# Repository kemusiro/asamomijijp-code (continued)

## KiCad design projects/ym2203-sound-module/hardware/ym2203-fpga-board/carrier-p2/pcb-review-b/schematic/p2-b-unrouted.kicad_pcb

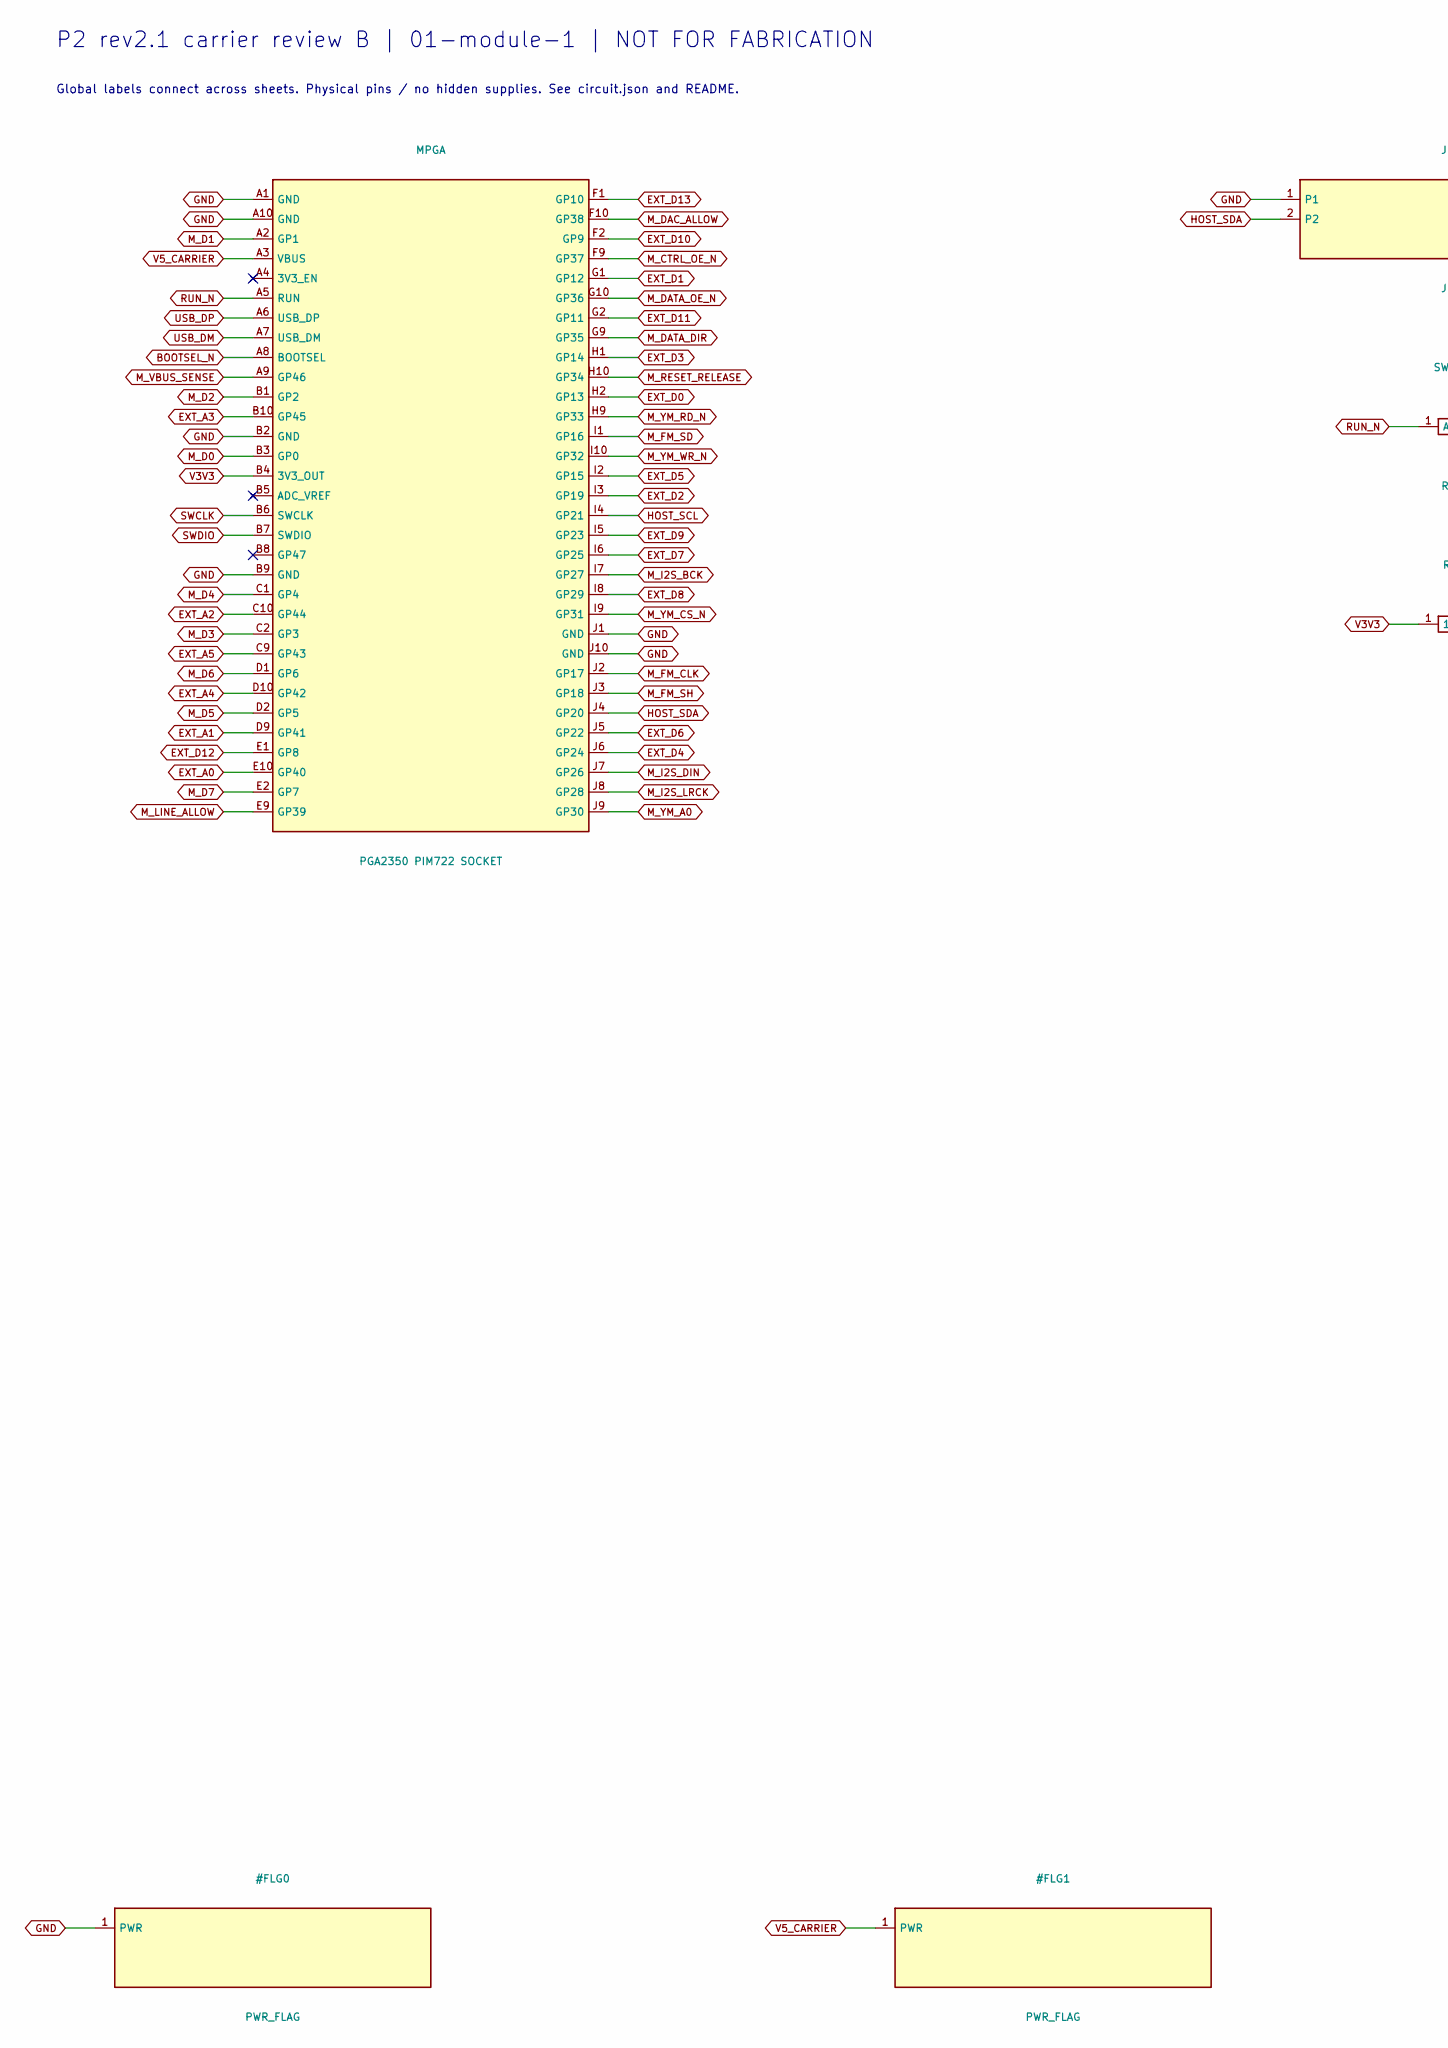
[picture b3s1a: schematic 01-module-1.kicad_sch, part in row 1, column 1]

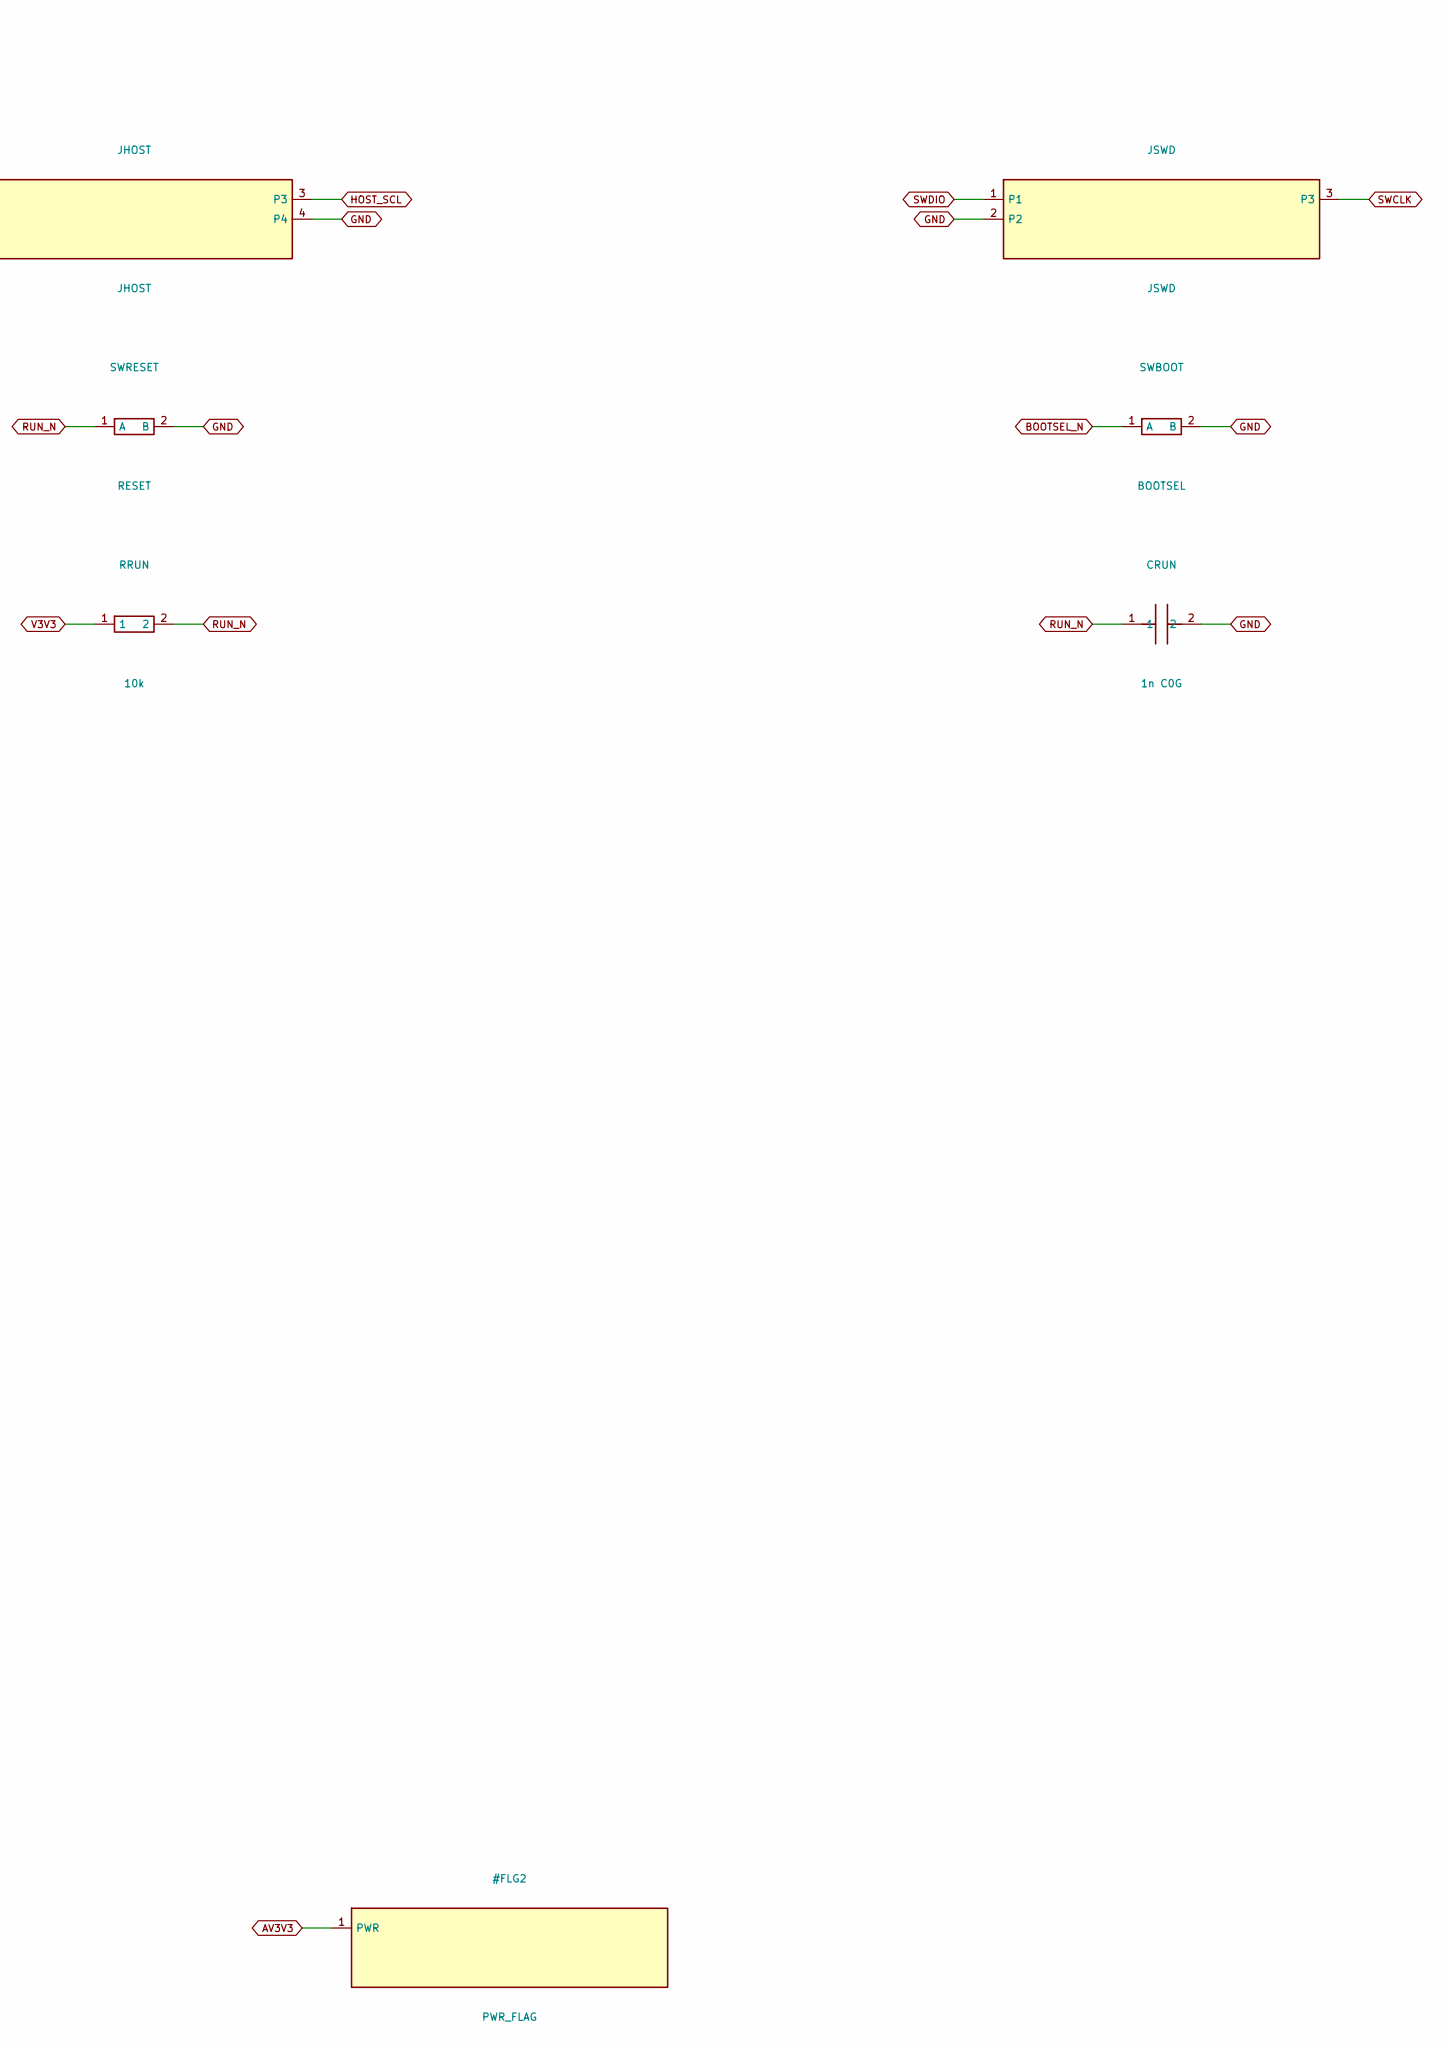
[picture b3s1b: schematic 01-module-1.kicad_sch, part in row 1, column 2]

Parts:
CRUN: 1n C0G; C_0805_2012Metric
JHOST: JHOST; PinHeader_1x04_P2.54mm_Vertical
JSWD: JSWD; PinHeader_1x03_P2.54mm_Vertical
MPGA: PGA2350 PIM722 SOCKET; PGA2350_Socket_64
RRUN: 10k; R_0805_2012Metric
SWBOOT: BOOTSEL; SW_PUSH_6mm_H4.3mm
SWRESET: RESET; SW_PUSH_6mm_H4.3mm

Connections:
BOOTSEL_N: MPGA.A8 (BOOTSEL), SWBOOT.1 (A)
EXT_A0: MPGA.E10 (GP40); also elsewhere on the board
EXT_A1: MPGA.D9 (GP41); also elsewhere on the board
EXT_A2: MPGA.C10 (GP44); also elsewhere on the board
EXT_A3: MPGA.B10 (GP45); also elsewhere on the board
EXT_A4: MPGA.D10 (GP42); also elsewhere on the board
EXT_A5: MPGA.C9 (GP43); also elsewhere on the board
EXT_D0: MPGA.H2 (GP13); also elsewhere on the board
EXT_D1: MPGA.G1 (GP12); also elsewhere on the board
EXT_D2: MPGA.I3 (GP19); also elsewhere on the board
EXT_D3: MPGA.H1 (GP14); also elsewhere on the board
EXT_D4: MPGA.J6 (GP24); also elsewhere on the board
EXT_D5: MPGA.I2 (GP15); also elsewhere on the board
EXT_D6: MPGA.J5 (GP22); also elsewhere on the board
EXT_D7: MPGA.I6 (GP25); also elsewhere on the board
EXT_D8: MPGA.I8 (GP29); also elsewhere on the board
EXT_D9: MPGA.I5 (GP23); also elsewhere on the board
EXT_D10: MPGA.F2 (GP9); also elsewhere on the board
EXT_D11: MPGA.G2 (GP11); also elsewhere on the board
EXT_D12: MPGA.E1 (GP8); also elsewhere on the board
EXT_D13: MPGA.F1 (GP10); also elsewhere on the board
GND: CRUN.2, JHOST.1, JHOST.4, JSWD.2, MPGA.A1 (GND), MPGA.A10 (GND), MPGA.B2 (GND), MPGA.B9 (GND), MPGA.J1 (GND), MPGA.J10 (GND), SWBOOT.2 (B), SWRESET.2 (B); also elsewhere on the board
HOST_SCL: JHOST.3, MPGA.I4 (GP21); also elsewhere on the board
HOST_SDA: JHOST.2, MPGA.J4 (GP20); also elsewhere on the board
M_CTRL_OE_N: MPGA.F9 (GP37); also elsewhere on the board
M_D0: MPGA.B3 (GP0); also elsewhere on the board
M_D1: MPGA.A2 (GP1); also elsewhere on the board
M_D2: MPGA.B1 (GP2); also elsewhere on the board
M_D3: MPGA.C2 (GP3); also elsewhere on the board
M_D4: MPGA.C1 (GP4); also elsewhere on the board
M_D5: MPGA.D2 (GP5); also elsewhere on the board
M_D6: MPGA.D1 (GP6); also elsewhere on the board
M_D7: MPGA.E2 (GP7); also elsewhere on the board
M_DAC_ALLOW: MPGA.F10 (GP38); also elsewhere on the board
M_DATA_DIR: MPGA.G9 (GP35); also elsewhere on the board
M_DATA_OE_N: MPGA.G10 (GP36); also elsewhere on the board
M_FM_CLK: MPGA.J2 (GP17); also elsewhere on the board
M_FM_SD: MPGA.I1 (GP16); also elsewhere on the board
M_FM_SH: MPGA.J3 (GP18); also elsewhere on the board
M_I2S_BCK: MPGA.I7 (GP27); also elsewhere on the board
M_I2S_DIN: MPGA.J7 (GP26); also elsewhere on the board
M_I2S_LRCK: MPGA.J8 (GP28); also elsewhere on the board
M_LINE_ALLOW: MPGA.E9 (GP39); also elsewhere on the board
M_RESET_RELEASE: MPGA.H10 (GP34); also elsewhere on the board
M_VBUS_SENSE: MPGA.A9 (GP46); also elsewhere on the board
M_YM_A0: MPGA.J9 (GP30); also elsewhere on the board
M_YM_CS_N: MPGA.I9 (GP31); also elsewhere on the board
M_YM_RD_N: MPGA.H9 (GP33); also elsewhere on the board
M_YM_WR_N: MPGA.I10 (GP32); also elsewhere on the board
RUN_N: CRUN.1, MPGA.A5 (RUN), RRUN.2, SWRESET.1 (A); also elsewhere on the board
SWCLK: JSWD.3, MPGA.B6 (SWCLK)
SWDIO: JSWD.1, MPGA.B7 (SWDIO)
USB_DM: MPGA.A7 (USB_DM); also elsewhere on the board
USB_DP: MPGA.A6 (USB_DP); also elsewhere on the board
V3V3: MPGA.B4 (3V3_OUT), RRUN.1; also elsewhere on the board
V5_CARRIER: MPGA.A3 (VBUS); also elsewhere on the board

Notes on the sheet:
P2 rev2.1 carrier review B | 01-module-1 | NOT FOR FABRICATION
Global labels connect across sheets. Physical pins / no hidden supplies. See circuit.json and README.

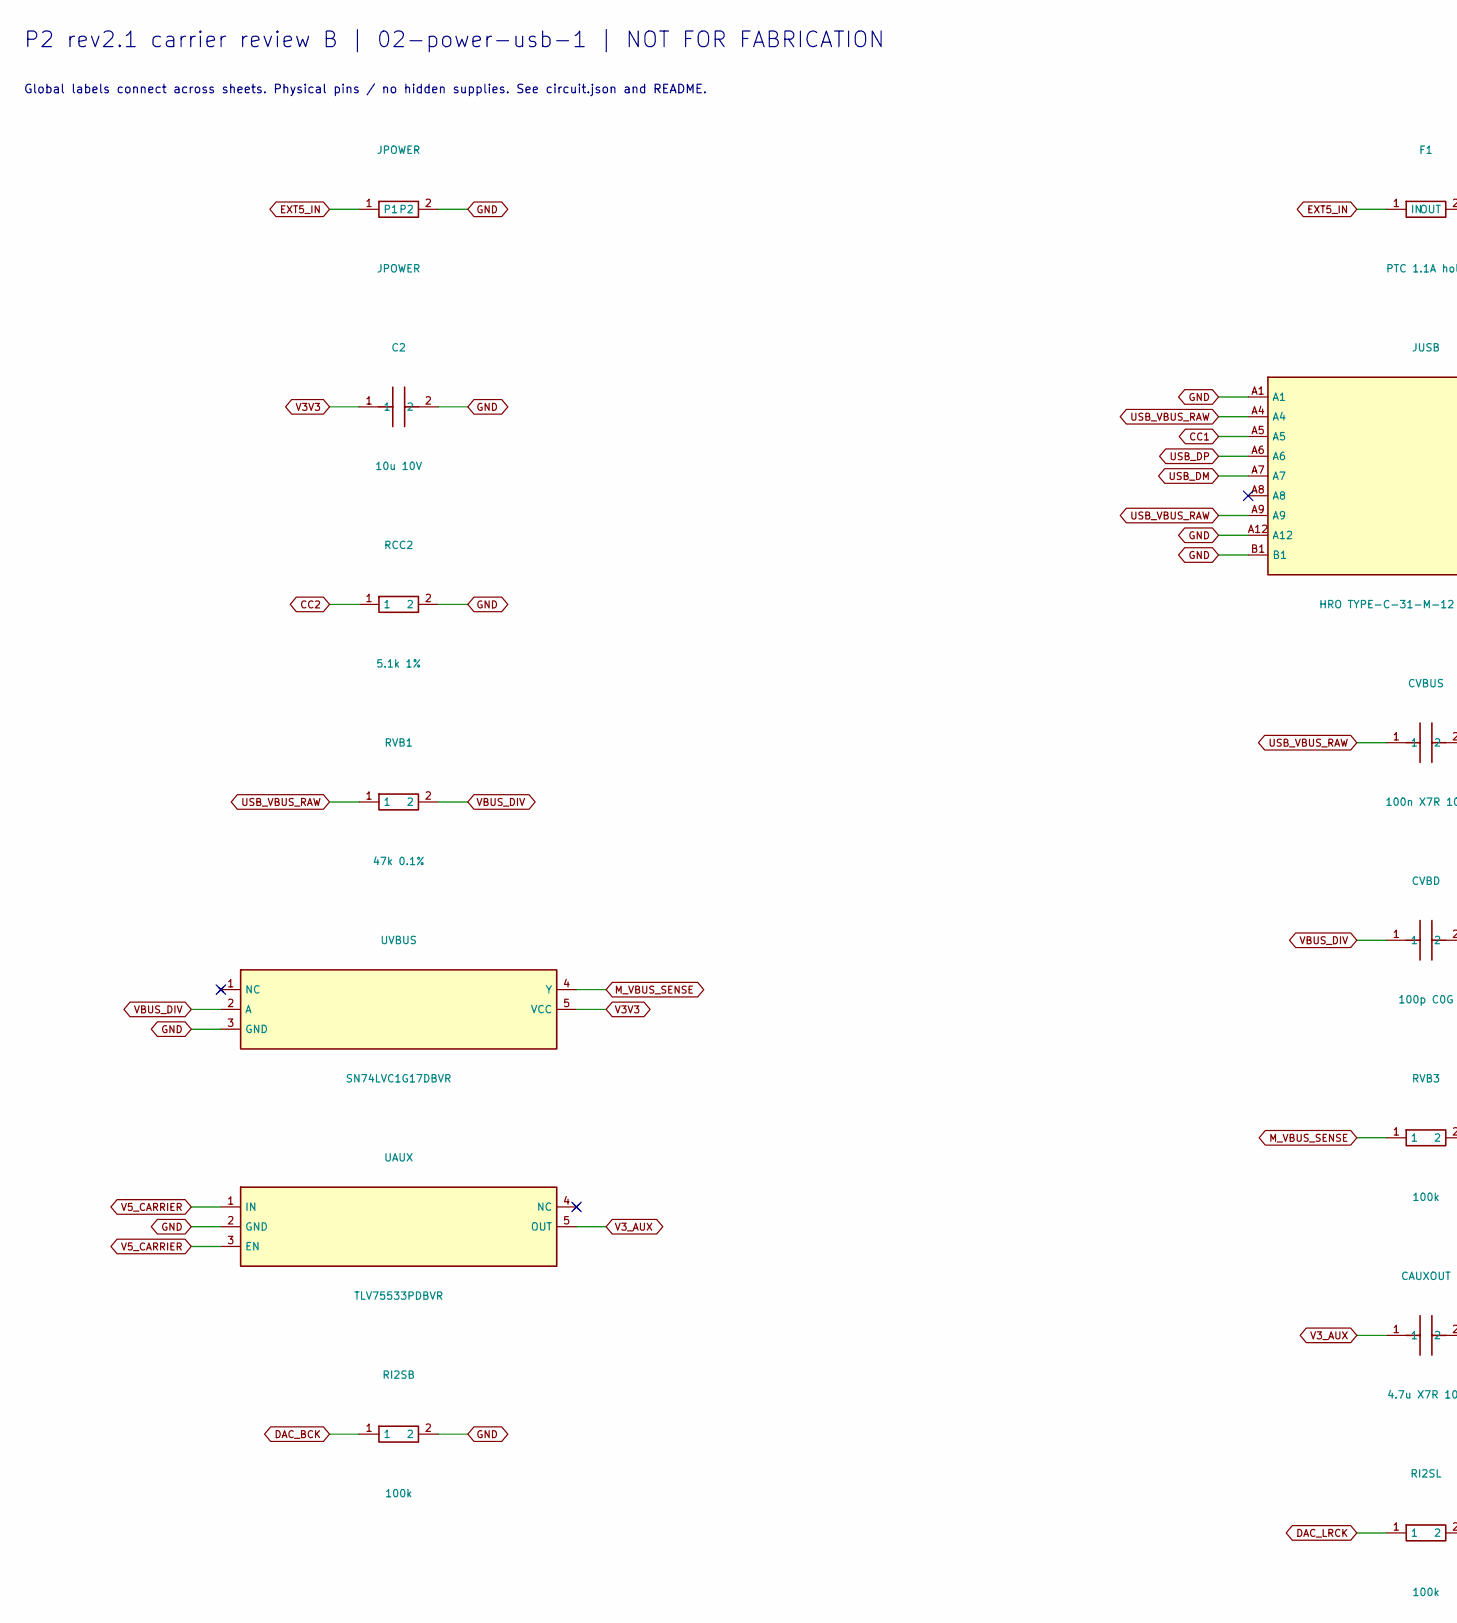
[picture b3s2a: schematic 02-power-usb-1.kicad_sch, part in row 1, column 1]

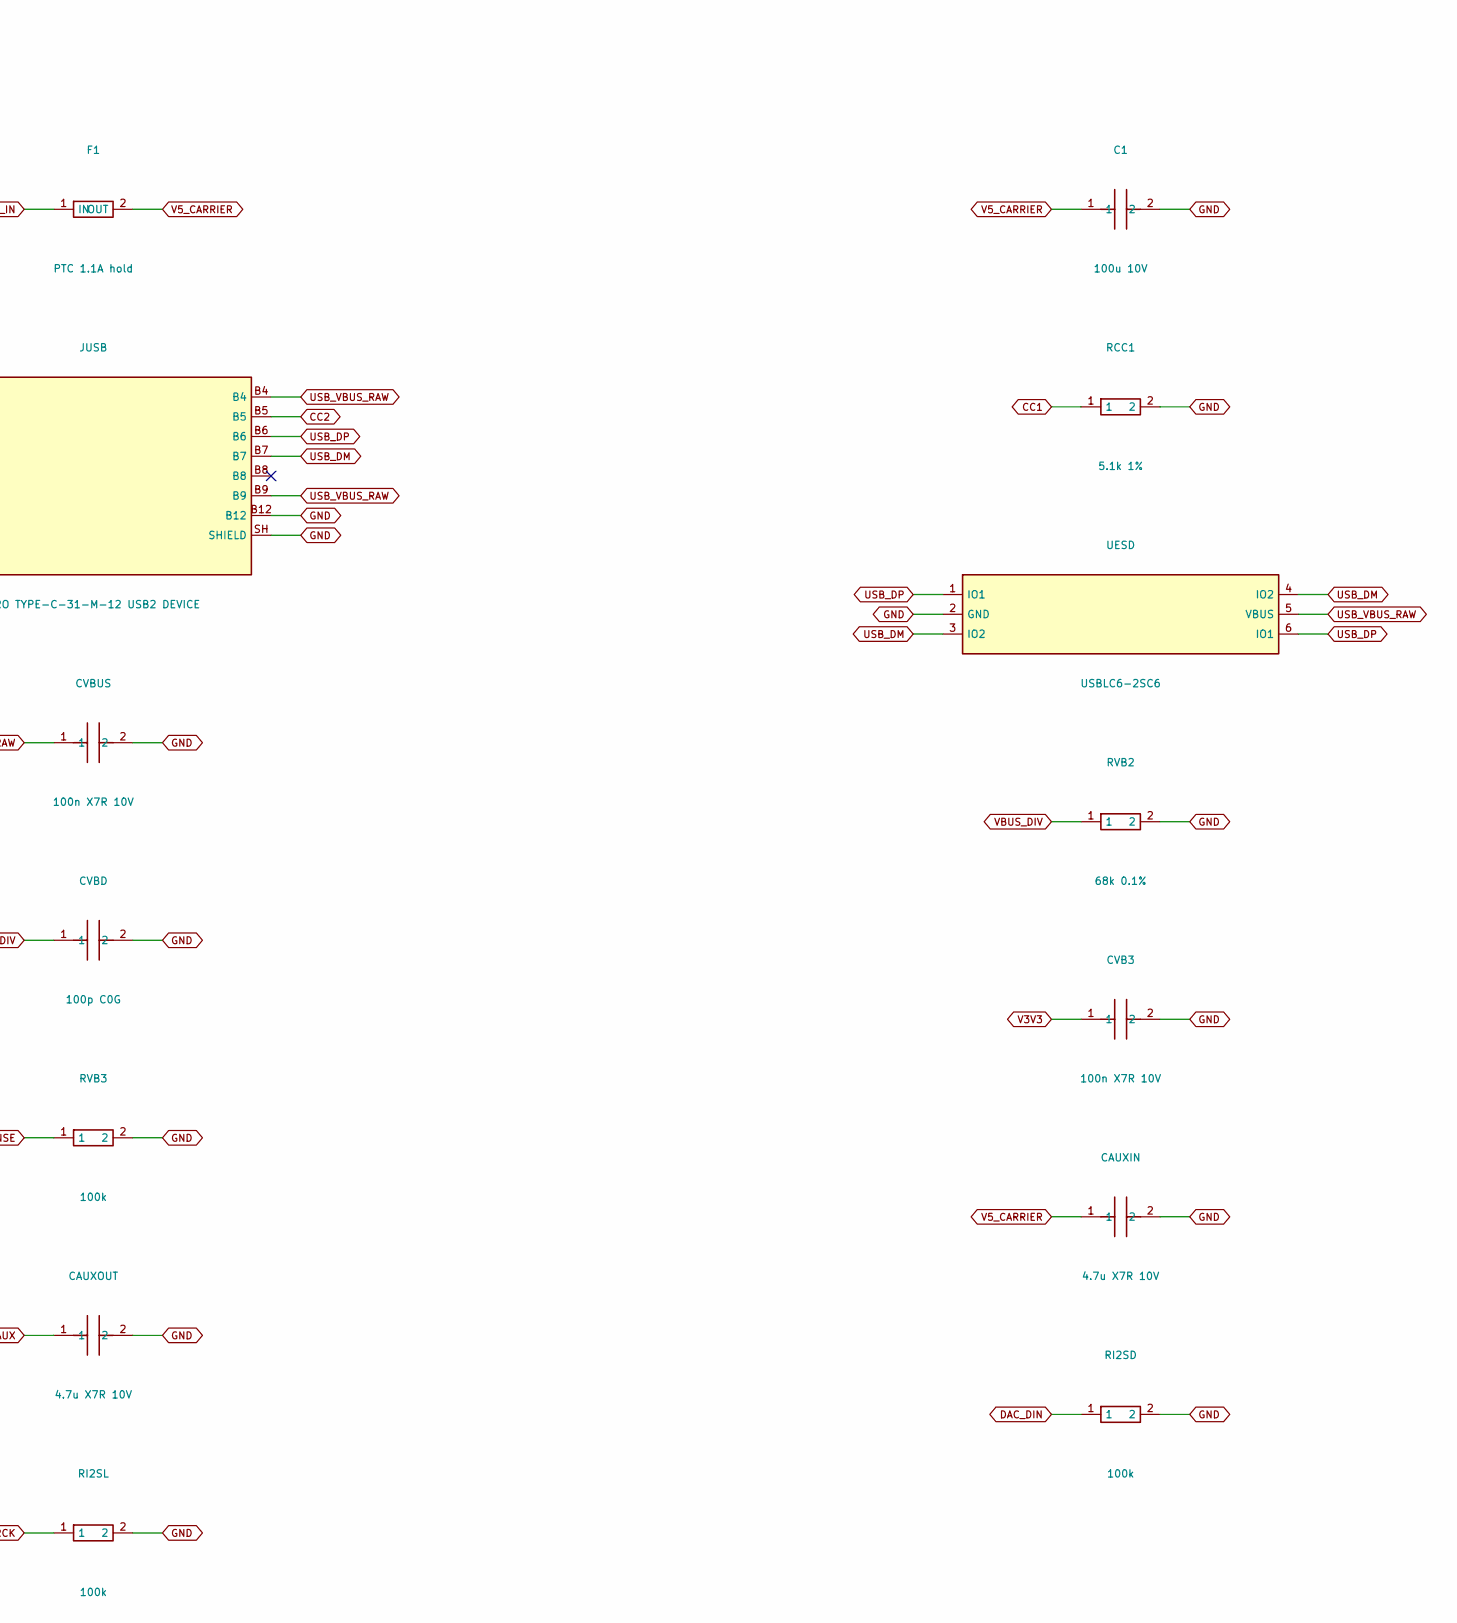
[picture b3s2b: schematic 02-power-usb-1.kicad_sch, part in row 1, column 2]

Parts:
C1: 100u 10V; CP_Radial_D6.3mm_P2.50mm
C2: 10u 10V; C_0805_2012Metric
CAUXIN: 4.7u X7R 10V; C_0805_2012Metric
CAUXOUT: 4.7u X7R 10V; C_0805_2012Metric
CVB3: 100n X7R 10V; C_0805_2012Metric
CVBD: 100p C0G; C_0805_2012Metric
CVBUS: 100n X7R 10V; C_0805_2012Metric
F1: PTC 1.1A hold; Fuse_1812_4532Metric
JPOWER: JPOWER; PinHeader_1x02_P2.54mm_Vertical
JUSB: HRO TYPE-C-31-M-12 USB2 DEVICE; USB_C_Receptacle_HRO_TYPE-C-31-M-12
RCC1, RCC2: 5.1k 1%; R_0805_2012Metric
RI2SB, RI2SD, RI2SL: 100k; R_0805_2012Metric
RVB1: 47k 0.1%; R_0805_2012Metric
RVB2: 68k 0.1%; R_0805_2012Metric
RVB3: 100k; R_0805_2012Metric
UAUX: TLV75533PDBVR; SOT-23-5
UESD: USBLC6-2SC6; SOT-23-6
UVBUS: SN74LVC1G17DBVR; SOT-23-5

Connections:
CC1: JUSB.A5, RCC1.1
CC2: JUSB.B5, RCC2.1
DAC_BCK: RI2SB.1; also elsewhere on the board
DAC_DIN: RI2SD.1; also elsewhere on the board
DAC_LRCK: RI2SL.1; also elsewhere on the board
EXT5_IN: F1.1 (IN), JPOWER.1
GND: C1.2, C2.2, CAUXIN.2, CAUXOUT.2, CVB3.2, CVBD.2, CVBUS.2, JPOWER.2, JUSB.A1, JUSB.A12, JUSB.B1, JUSB.B12, JUSB.SH (SHIELD), RCC1.2, RCC2.2, RI2SB.2, RI2SD.2, RI2SL.2, RVB2.2, RVB3.2, UAUX.2 (GND), UESD.2 (GND), UVBUS.3 (GND); also elsewhere on the board
M_VBUS_SENSE: RVB3.1, UVBUS.4 (Y); also elsewhere on the board
USB_DM: JUSB.A7, JUSB.B7, UESD.3 (IO2), UESD.4 (IO2); also elsewhere on the board
USB_DP: JUSB.A6, JUSB.B6, UESD.1 (IO1), UESD.6 (IO1); also elsewhere on the board
USB_VBUS_RAW: CVBUS.1, JUSB.A4, JUSB.A9, JUSB.B4, JUSB.B9, RVB1.1, UESD.5 (VBUS)
V3V3: C2.1, CVB3.1, UVBUS.5 (VCC); also elsewhere on the board
V3_AUX: CAUXOUT.1, UAUX.5 (OUT); also elsewhere on the board
V5_CARRIER: C1.1, CAUXIN.1, F1.2 (OUT), UAUX.1 (IN), UAUX.3 (EN); also elsewhere on the board
VBUS_DIV: CVBD.1, RVB1.2, RVB2.1, UVBUS.2 (A)

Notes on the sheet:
P2 rev2.1 carrier review B | 02-power-usb-1 | NOT FOR FABRICATION
Global labels connect across sheets. Physical pins / no hidden supplies. See circuit.json and README.

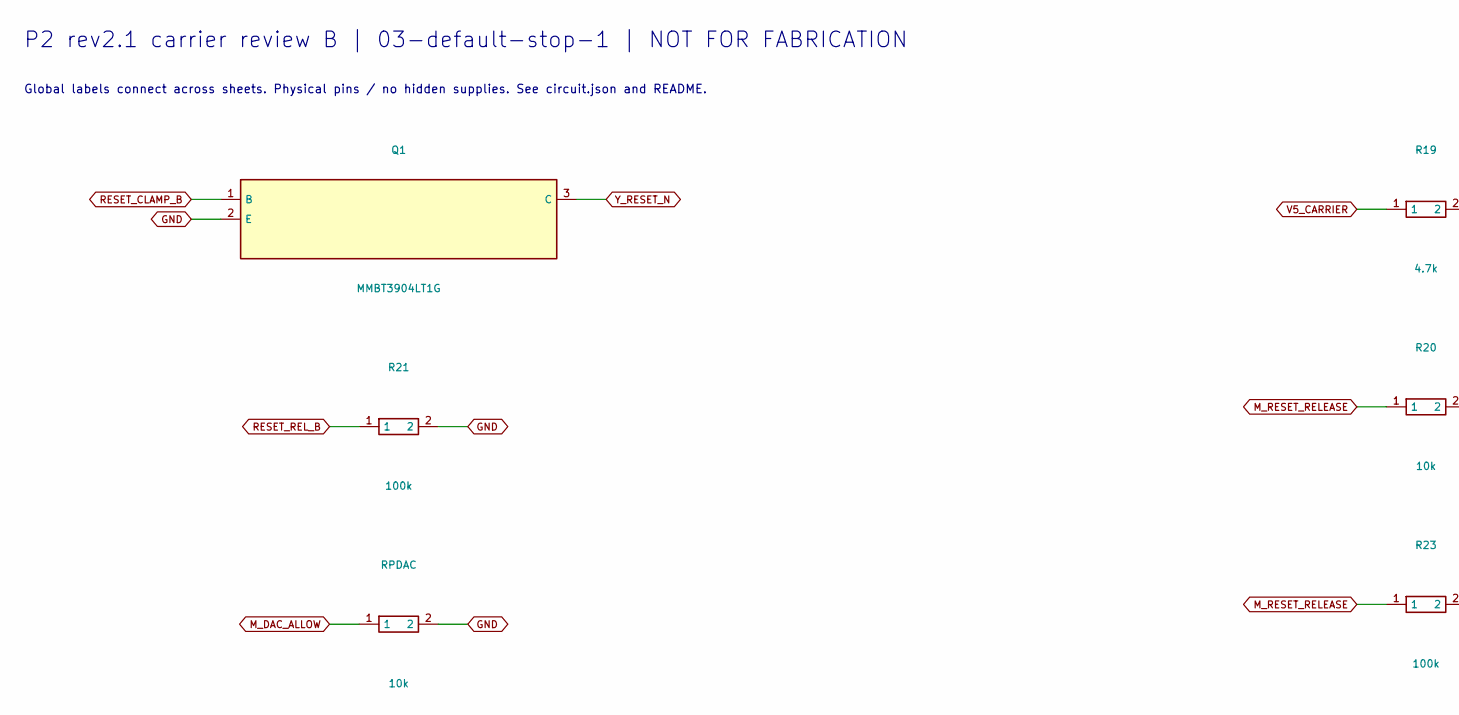
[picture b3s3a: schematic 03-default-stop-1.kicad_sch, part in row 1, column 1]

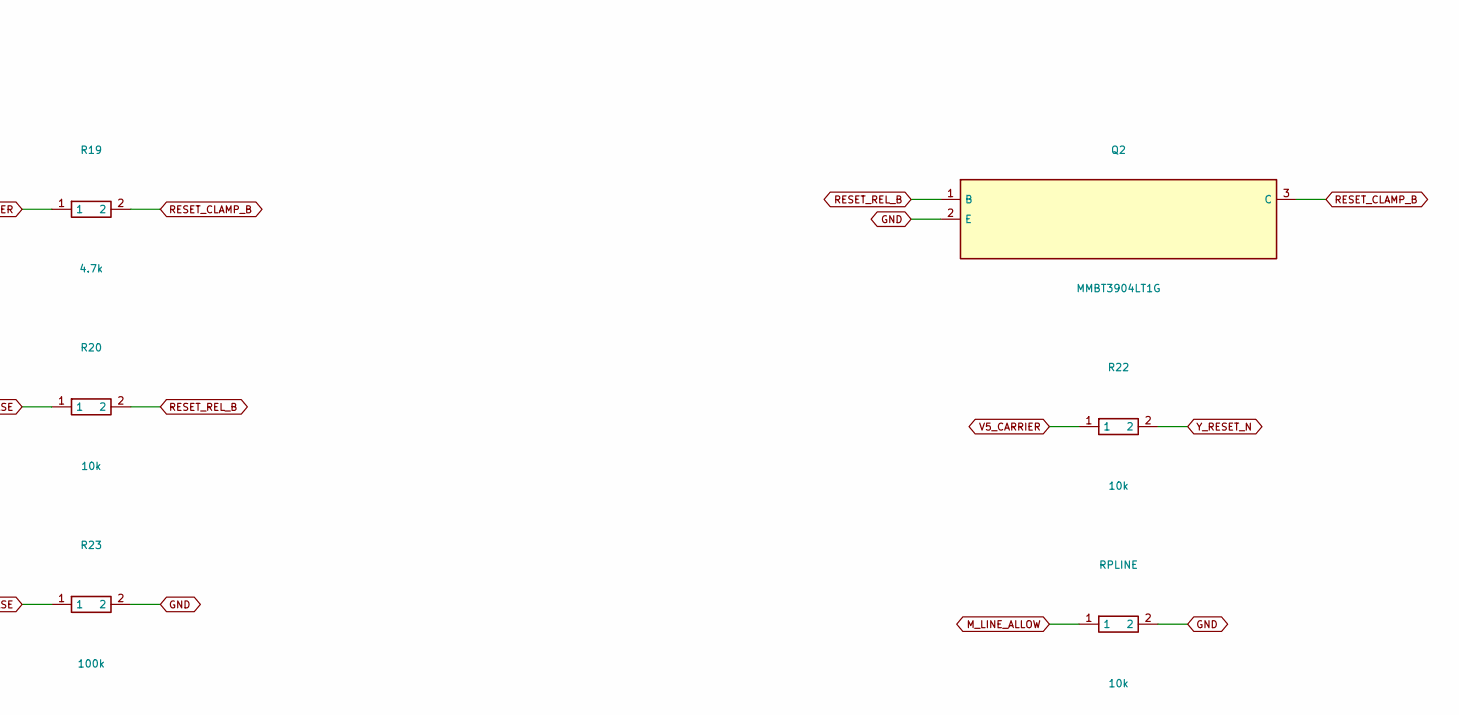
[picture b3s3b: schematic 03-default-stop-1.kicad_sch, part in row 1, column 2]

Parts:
Q1, Q2: MMBT3904LT1G; SOT-23
R19: 4.7k; R_0805_2012Metric
R20, R22: 10k; R_0805_2012Metric
R21, R23: 100k; R_0805_2012Metric
RPDAC: 10k; R_0805_2012Metric
RPLINE: 10k; R_0805_2012Metric

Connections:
GND: Q1.2 (E), Q2.2 (E), R21.2, R23.2, RPDAC.2, RPLINE.2; also elsewhere on the board
M_DAC_ALLOW: RPDAC.1; also elsewhere on the board
M_LINE_ALLOW: RPLINE.1; also elsewhere on the board
M_RESET_RELEASE: R20.1, R23.1; also elsewhere on the board
RESET_CLAMP_B: Q1.1 (B), Q2.3 (C), R19.2
RESET_REL_B: Q2.1 (B), R20.2, R21.1
V5_CARRIER: R19.1, R22.1; also elsewhere on the board
Y_RESET_N: Q1.3 (C), R22.2; also elsewhere on the board

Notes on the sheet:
P2 rev2.1 carrier review B | 03-default-stop-1 | NOT FOR FABRICATION
Global labels connect across sheets. Physical pins / no hidden supplies. See circuit.json and README.
